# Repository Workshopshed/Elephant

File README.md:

# Elephant

This ESP32 controlled elephant was created for Diyode Magazine and was published in issue #26 and #28.  Daniel Koch took up the challenge to try to build this from my instructions and in the process we came up with a bunch of enhancements to make it easier to print and assemble. Daniel and Murray Roberts also ensured the wording of the instructions was top notch.

https://diyodemag.com/projects/part_1_walking_wildlife

https://diyodemag.com/projects/part_2_walking_wildlife

The elephant is controlled from a simple web page hosted on the ESP32 and Ajax calls are used to respond to the buttons.

A spin off project for the servo power distribution board also appeared in issue #26 with Daniel Koch providing a cloned version using stripboard.
https://diyodemag.com/projects/servo_power

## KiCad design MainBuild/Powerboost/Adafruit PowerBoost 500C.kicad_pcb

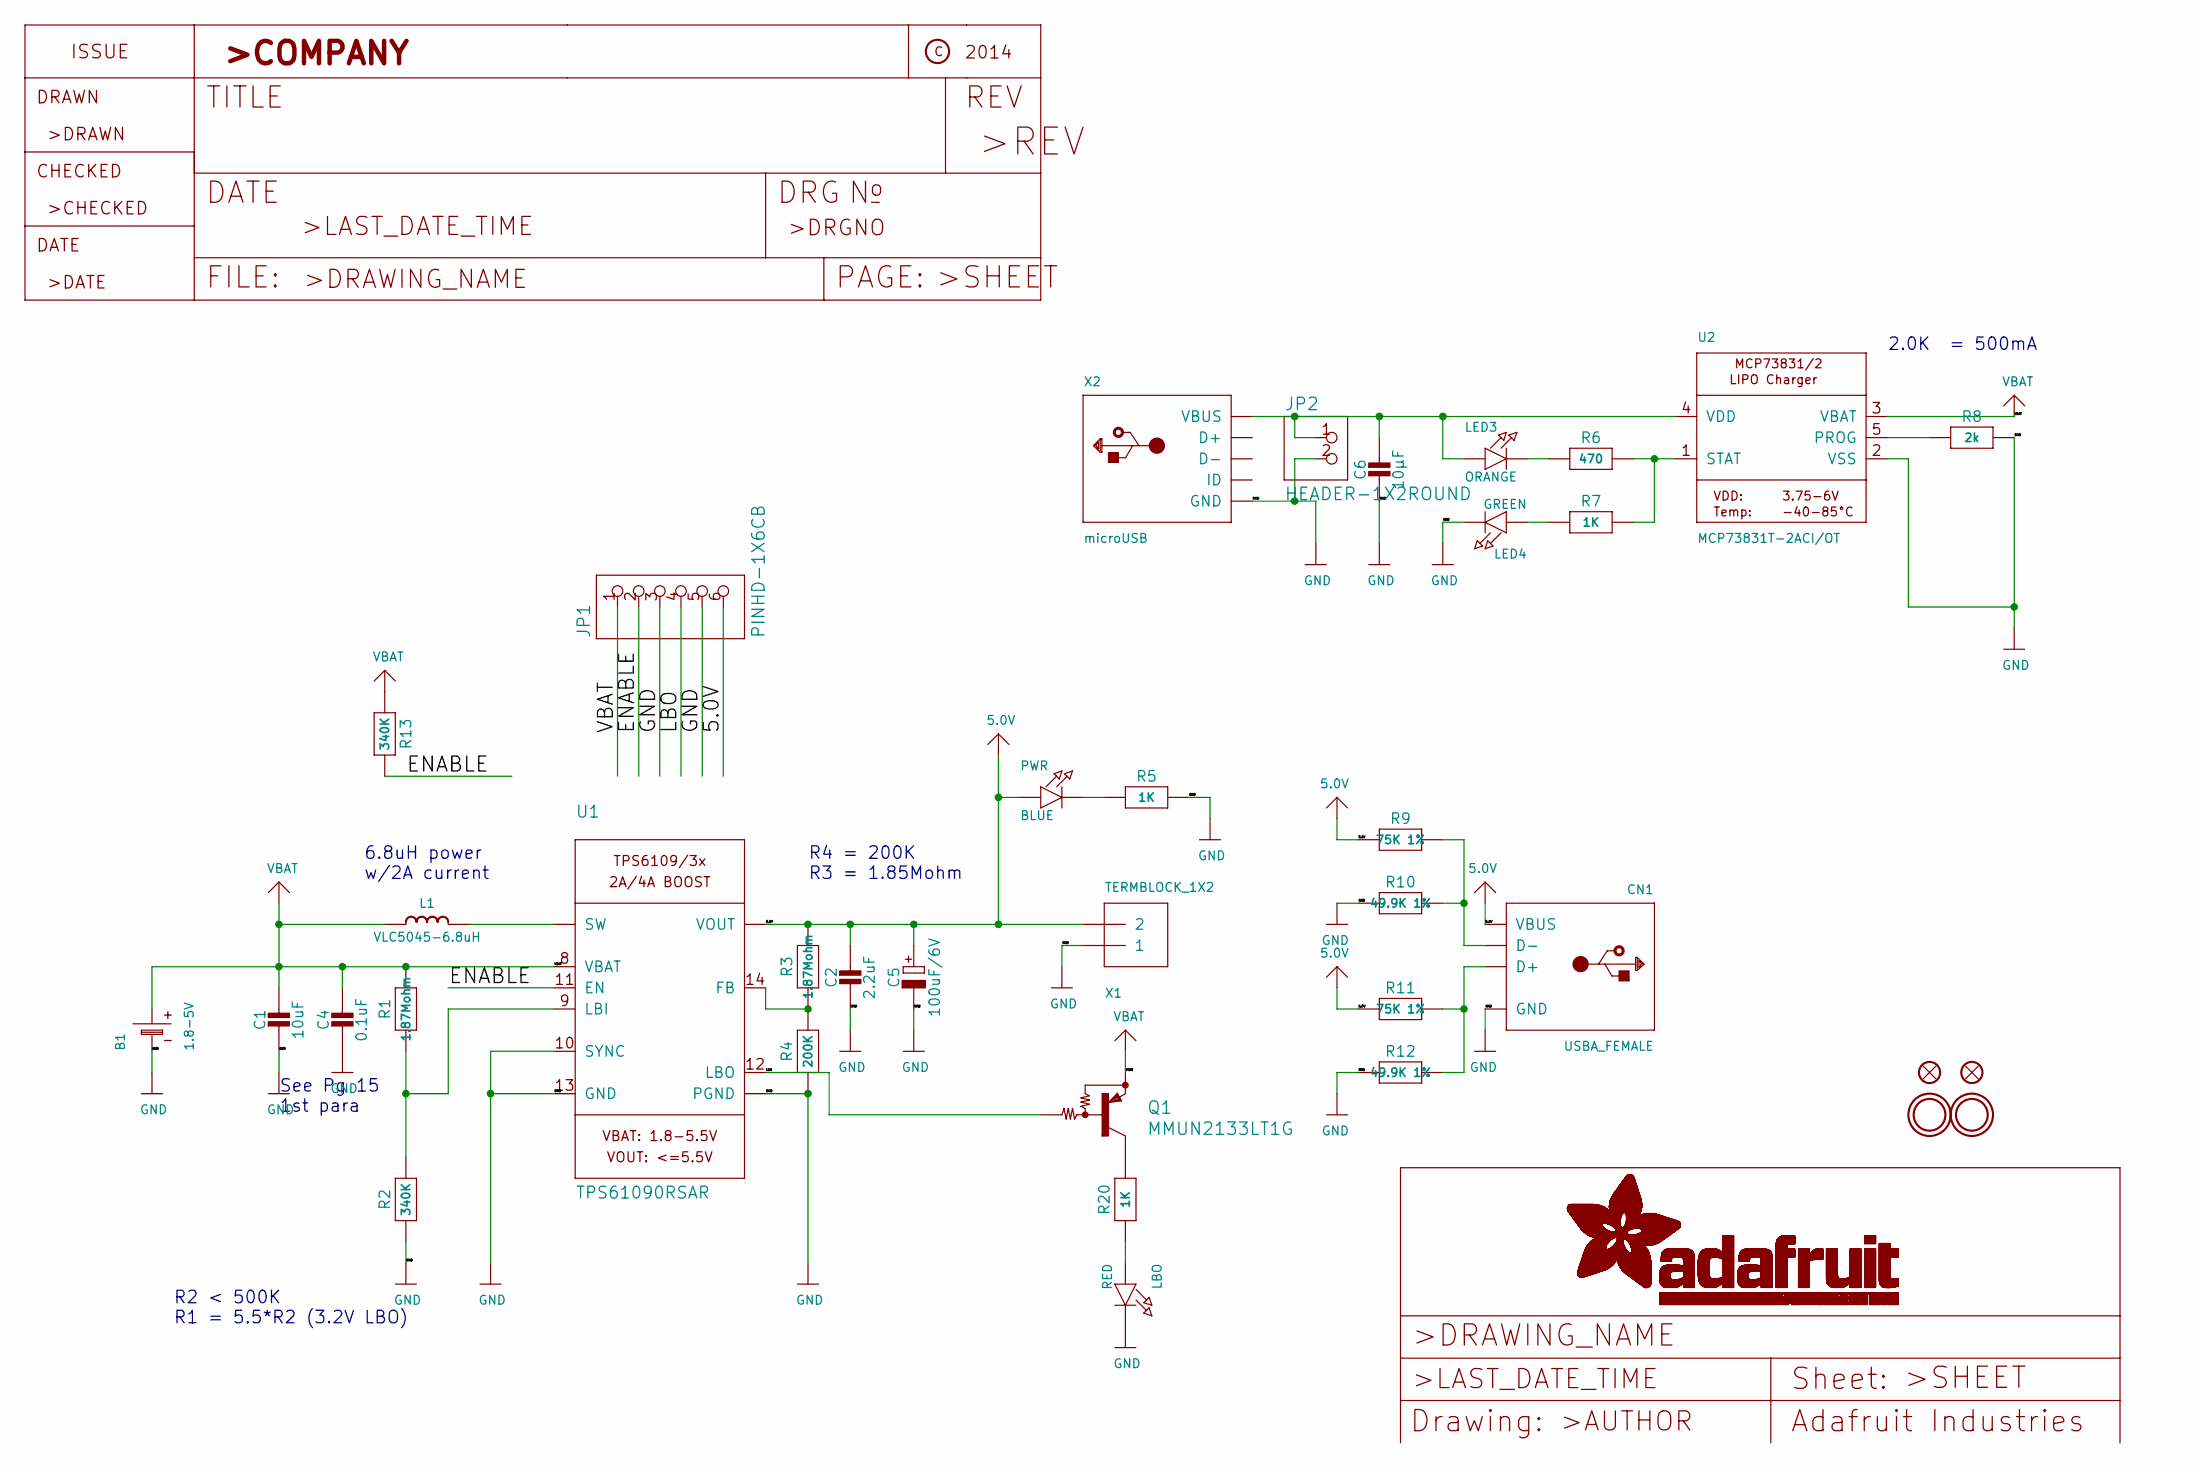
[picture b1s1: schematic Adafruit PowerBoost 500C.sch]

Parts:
B1: 1.8-5V; JSTPH2
C1: 10uF; 0805-NO
C2: 2.2uF; 0805-NO
C4: 0.1uF; 0805-NO
C5: 100uF/6V; EIA3528-21_B-R
C6: 10µF; 0805-NO
CN1: USBA_FEMALE; USB_HOST-PTH
FID2, FID3: FIDUCIAL\"\"; FIDUCIAL_1MM
JP1: PINHD-1X6CB; 1X06-CLEANBIG
JP2: HEADER-1X2ROUND; 1X02_ROUND
L1: VLC5045-6.8uH; INDUCTOR_5X5MM_TDK_VLC5045
LBO: RED; CHIPLED_0805_NOOUTLINE
LED3: ORANGE; CHIPLED_0805_NOOUTLINE
LED4: GREEN; CHIPLED_0805_NOOUTLINE
PWR: BLUE; CHIPLED_0805_NOOUTLINE
Q1: MMUN2133LT1G; SC59-BEC
R1, R3: 1.87Mohm; 0805-NO
R2, R13: 340K; 0805-NO
R4: 200K; 0805-NO
R5, R7, R20: 1K; 0805-NO
R6: 470; 0805-NO
R8: 2k; 0805-NO
R9, R11: 75K 1%; 0805-NO
R10, R12: 49.9K 1%; 0805-NO
U1: TPS61090RSAR; PVQFN-16
U2: MCP73831T-2ACI/OT; SOT23-5
U$10, U$12: MOUNTINGHOLE2.5; MOUNTINGHOLE_2.5_PLATED
X1: TERMBLOCK_1X2; TERMBLOCK_1X2-3.5MM
X2: microUSB; 4UCONN_20329

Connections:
5.0V: C2.1, C5.+, CN1.VBUS, JP1.6, PWR.A, R3.2, R9.2, R11.2, U1.1 (VOUT), U1.15 (VOUT), U1.16 (VOUT), X1.2; also elsewhere on the board
/ENABLE: JP1.2, R13.2, U1.11 (EN)
/LBO: JP1.4, Q1.B, U1.12 (LBO)
GND: B1.1 (-), C1.2, C2.2, C4.2, C5.-, C6.2, CN1.GND, JP1.3, JP1.5, JP2.2, LBO.C, LED4.C, R2.1, R4.1, R5.2, R8.2, R10.2, R12.2, U1.5 (PGND), U1.6 (PGND), U1.7 (PGND), U1.10 (SYNC), U1.13 (GND), U1.P$18 (PGND), U1.P$19 (PGND), U1.P$20 (PGND), U1.P$21 (PGND), U1.P$22 (PGND), U1.THERMAL (PGND), U2.2 (VSS), X1.1, X2.BASE@1 (GND), X2.BASE@2 (GND), X2.GND, X2.SPRT@1 (GND), X2.SPRT@2 (GND), X2.SPRT@3 (GND), X2.SPRT@4 (GND); also elsewhere on the board
unnamed: C6.1, JP2.1, LED3.A, U2.4 (VDD), X2.VBUS
unnamed: CN1.D+, R11.1, R12.1
unnamed: CN1.D-, R9.1, R10.1
unnamed: L1.P$2 (2), U1.3 (SW), U1.4 (SW)
unnamed 8: LBO.A, R20.1; also elsewhere on the board
unnamed: LED3.C, R6.1
unnamed: LED4.A, R7.1
unnamed 11: PWR.C, R5.1; also elsewhere on the board
unnamed: Q1.C, R20.2
unnamed: R1.1, R2.2, U1.9 (LBI)
unnamed: R3.1, R4.2, U1.14 (FB)
unnamed: R6.2, R7.2, U2.1 (STAT)
unnamed: R8.1, U2.5 (PROG)
VBAT: B1.2 (+), C1.1, C4.1, JP1.1, L1.P$1 (1), Q1.E, R1.2, R13.1, U1.8 (VBAT), U2.3 (VBAT)

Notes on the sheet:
See Pg 15 1st para
6.8uH power w/2A current
R2 < 500K R1 = 5.5*R2 (3.2V LBO)
R4 = 200K R3 = 1.85Mohm
2.0K = 500mA

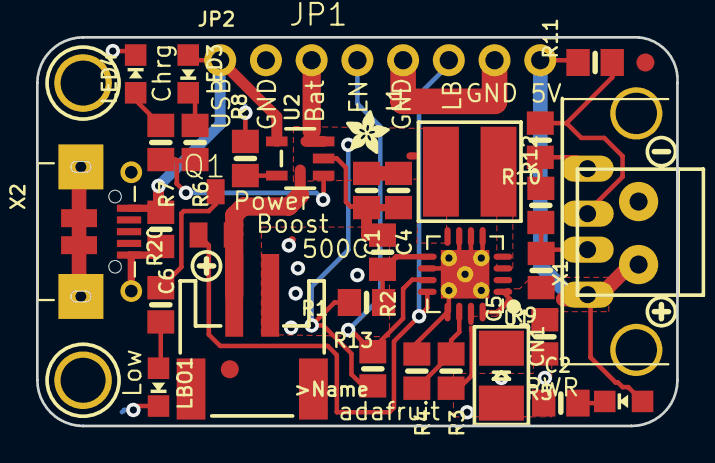
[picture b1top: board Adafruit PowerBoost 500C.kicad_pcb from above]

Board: 2 copper layers, 35.6 x 21.6 mm, 42 parts (0 on the bottom side), 18 nets.

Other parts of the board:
LBO1: RED; CHIPLED_0805_NOOUTLINE
PWR1: BLUE; CHIPLED_0805_NOOUTLINE
U$13, U$25: SYMBOL_PLUS
U$26: SYMBOL_MINUS
U$28: ADAFRUIT_2.5MM
U$29: ADAFRUIT_5MM

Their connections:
5.0V: PWR1.A; also elsewhere on the board
GND: LBO1.C; also elsewhere on the board
unnamed 8: LBO1.A; also elsewhere on the board
unnamed 11: PWR1.C; also elsewhere on the board

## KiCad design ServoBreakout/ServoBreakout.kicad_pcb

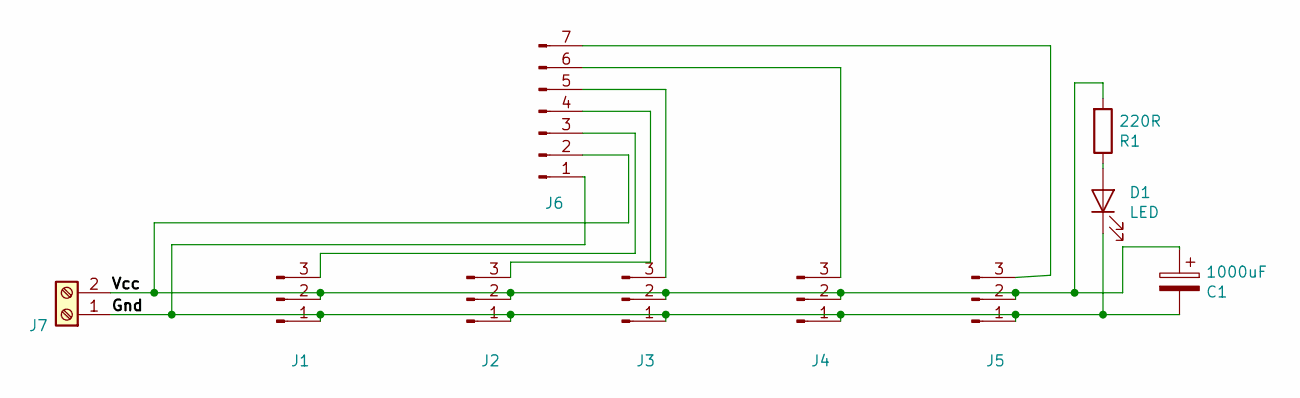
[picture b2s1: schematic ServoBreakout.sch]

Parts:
C1: 1000uF; CP_Radial_D10.0mm_P3.80mm
D1: LED; LED_D3.0mm
J1, J2, J3, J4, J5: Conn_01x03_Male; PinHeader_1x03_P2.54mm_Vertical
J6: Conn_01x07_Male; PinHeader_1x07_P2.54mm_Vertical
J7: Screw_Terminal_01x02; TerminalBlock_bornier-2_P5.08mm
R1: 220R; R_Axial_DIN0309_L9.0mm_D3.2mm_P12.70mm_Horizontal

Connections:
/Gnd: C1.2, D1.1 (K), J1.1, J2.1, J3.1, J4.1, J5.1, J6.1, J7.1
/Vcc: C1.1, J1.2, J2.2, J3.2, J4.2, J5.2, J6.2, J7.2, R1.2
unnamed: D1.2 (A), R1.1
unnamed: J1.3, J6.3
unnamed: J2.3, J6.4
unnamed: J3.3, J6.5
unnamed: J4.3, J6.6
unnamed: J5.3, J6.7

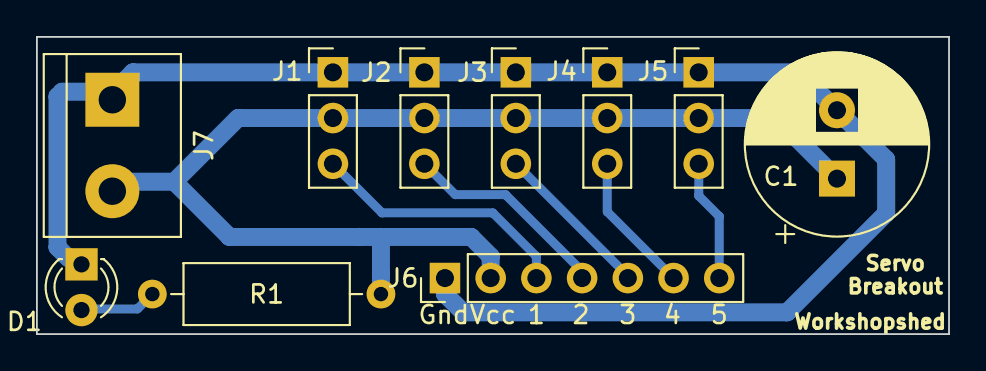
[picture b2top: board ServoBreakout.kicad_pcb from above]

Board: 2 copper layers, 50.7 x 16.5 mm, 10 parts (0 on the bottom side), 8 nets.

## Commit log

2019-08-09 Initial files
2019-08-09 Code, Models and Schematics
2019-09-08 Revert "Update Lower Body.stl"
    This reverts commit 1fc1be777c2246e224255c42bd3ced255f698e47.
2019-09-28 Updated Models
    doubled up the pawl to stop it from flopping around on the bracket
    Added a hole for a servo horn into the leg
2019-10-12 Update Upper Leg.stl
    New holes
2019-10-12 Models
    Settled models on the bed
